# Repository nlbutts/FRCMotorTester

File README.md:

# Brushless Buddy
This is a small PCB with a display and two rotary encoders. The device
is designed to help teams quickly prototype BLC designs using the Rev SparkMax
motor controllers. Although it could be expanded to support other devices.

# Design
The block diagram is shown below. The design consists of an input buck regulator.
The regulator should be good up to 24V, but was designed to work at 12V. There
is reverse battery protection, so it should handle accidentially connecting
the battery up in reverse.

The buck generates 5V which is used for the CAN transceiver. The 5V is fed
to two LDO's to generate 3.3V for the processor and 3.0V for the LCD backlight.

There are two status LEDs on the board, two rotary encoders, and a 128x32 pixel
graphical LCD. An STM32F446 processor powers everything.

There are three user accessible connectors:
Power J2:
| Pin | Use |
| -- | -- |
| 1 | Ground |
| 2 | Power |

The mate is a **JST PHR-2**

CAN J10:
| Pin | Use |
| -- | -- |
| 1 | CAN High |
| 2 | CAN Low |
| 3 | CAN High |
| 4 | CAN Low |

The pinout is the same as the Spark MAX and uses the same connector.
The mate is a **JST PHR-4**

Aux J3:
| Pin | Use |
| -- | -- |
| 1 | 3.3V |
| 2 | Ground |
| 3 | GPIO1 |
| 4 | GPIO2 |
| 5 | GPIO3 |
| 6 | Analog Input |

The mate is a **JST PHR-6**
The auxiliary connector is used for future use cases. It just made sense to
throw this connector on.

The picture below shows the location of the connectors.

# Software
The design runs Micropython. To re-build the code do the following:
1) Download the ARM GCC compiler [GCC](https://developer.arm.com/-/media/Files/downloads/gnu/13.3.rel1/binrel/arm-gnu-toolchain-13.3.rel1-x86_64-arm-none-eabi.tar.xz)
2) Decompress the toolchain to some known location, we will call this *<gcc_emd>*
3) Open a command prompt and update your path: `export PATH=<gcc_emd>/bin:$PATH`
4) Check out this repo, we will call this directory *<repo>*
5) Navigate to *<repo>/software/micropython
6) `make -C mpy-cross -j`
7) `BOARD=FRCMOTOR make -C ports/stm32/ -j`
8) Connect the Tagconnect to the board.
9) Program **firmware.elf** using the STM32CubeProgrammer.

## SWD Debug
It is assumed you are using a JLink and it is installed in **/opt/SEGGER/JLink**
In the software directory:
1) Run **gdbstart.sh** in one terminal
2) Run debug.sh in other terminal. You now have the full power of GDB at your literial finger tips

## Python

This device runs micropython. So the main program is a Python program. The
main program is called **main.py**, catchy aint it?

There are two levels of software upgrades. If you need to upgrade the Python code,
simply update main.py and copy it over to the **PYBFLASH** device.

If you need to update Micropython, then use a terminal program to open the REPL terminal.
Hit CTRL-C to stop the program. Then type
```
import machine
machine.bootloader()
```

This will put the processor in DFU upgrade mode. You can now use STM32CubeProgrammer to program
the DFU file. If the upgrade fails, then the device will have to be JTAGed. The next rev
of the PCB will fix a defect and a physical button will allow the unit to be booted in DFU mode.

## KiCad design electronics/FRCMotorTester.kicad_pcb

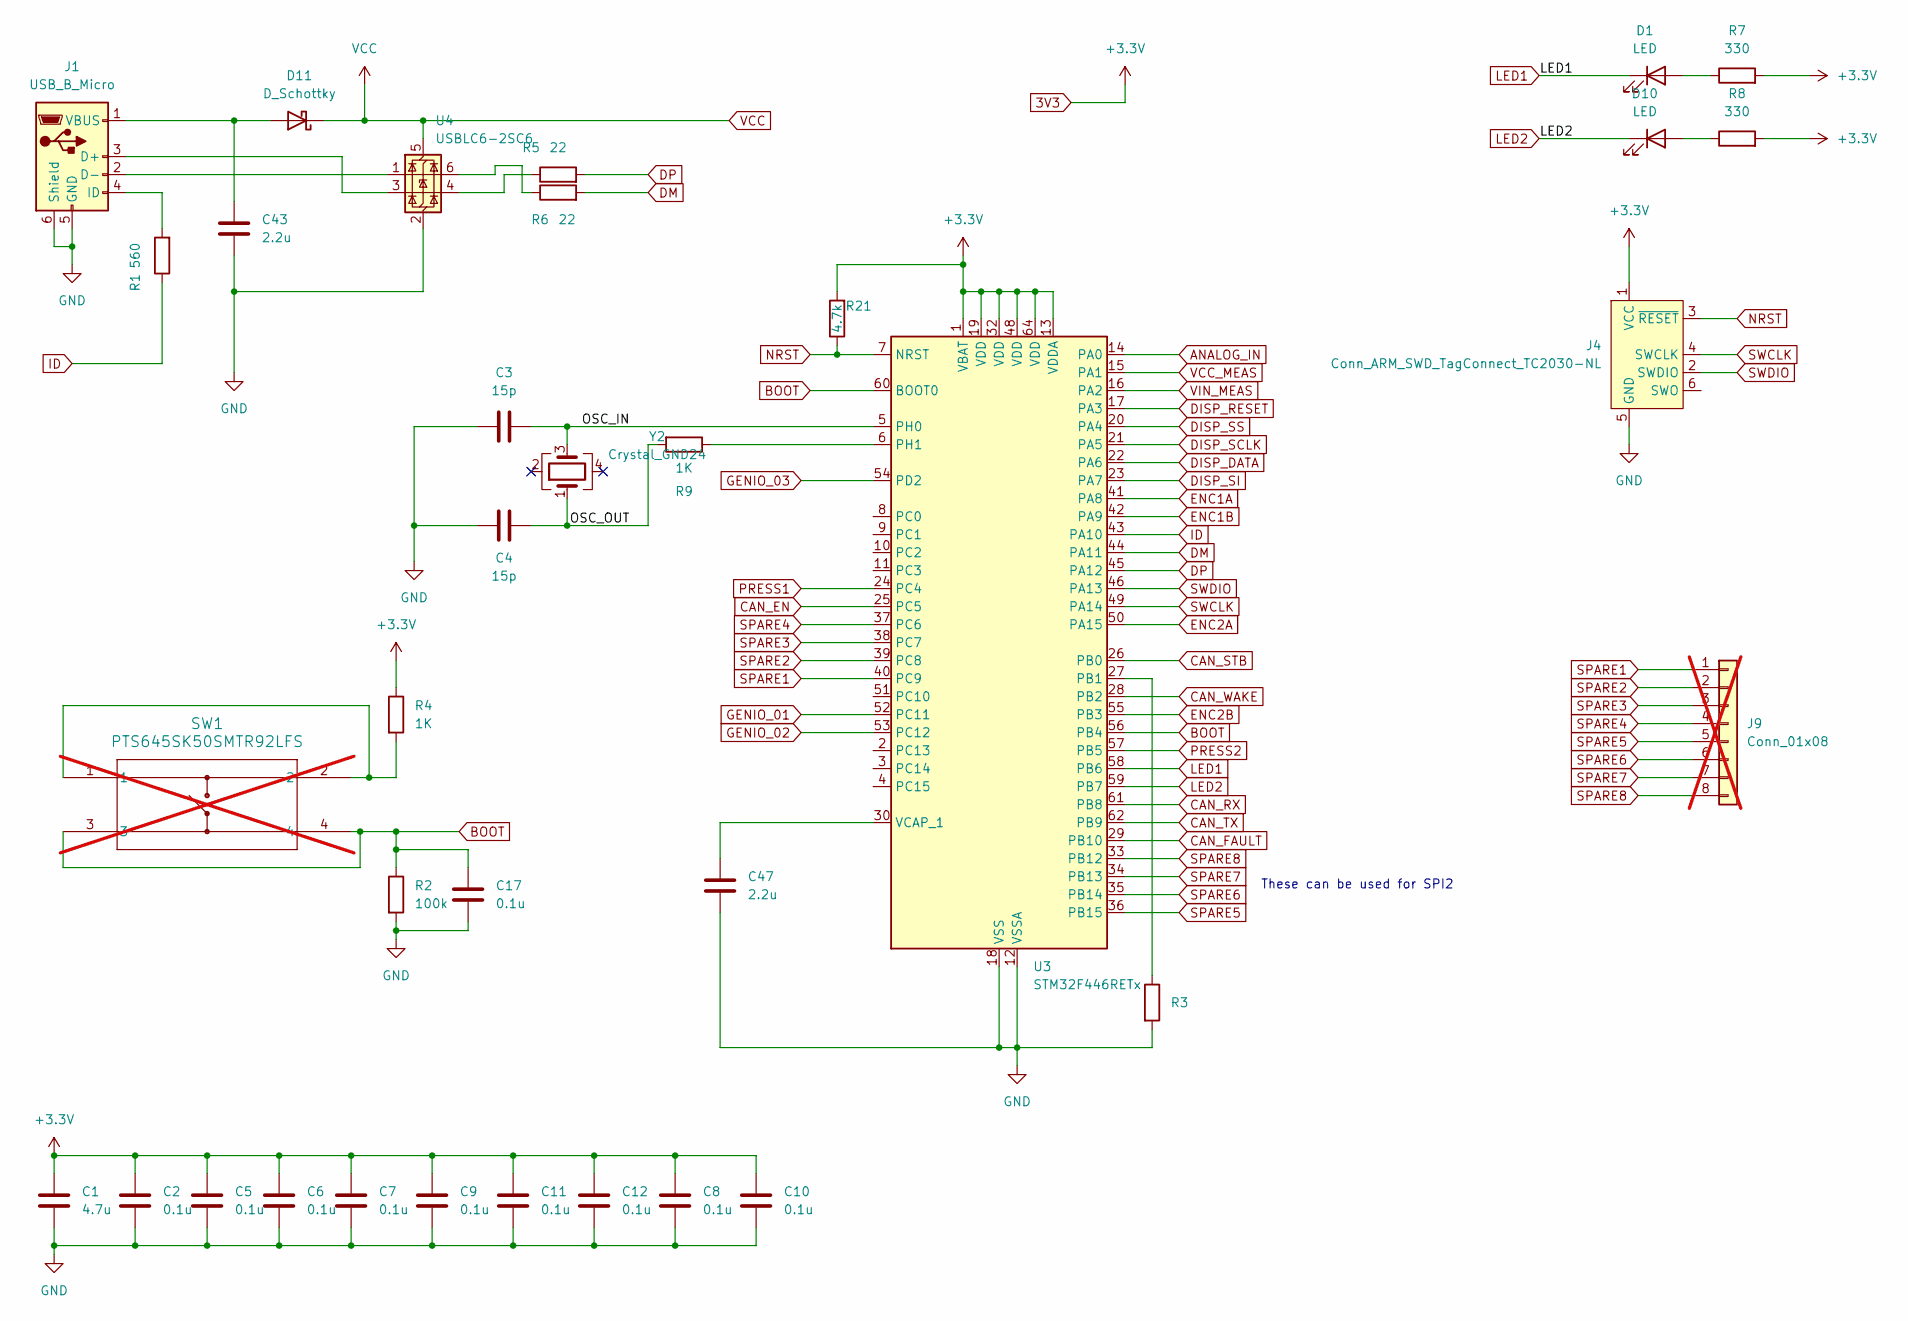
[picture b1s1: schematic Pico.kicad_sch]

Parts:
C1: 4.7u; C_0805_2012Metric; JLC C1779
C2, C5, C6, C7, C8, C9, C10, C11, C12, C17: 0.1u; C_0402_1005Metric; JLC C1525
C3, C4: 15p; C_0402_1005Metric; JLC C1548
C43, C47: 2.2u; C_0603_1608Metric; JLC C23630
D1, D10: LED; LED_0603_1608Metric; JLC C2286
D11: D_Schottky; D_SOD-123; Digikey B0540W-FDICT-ND
J1: USB_B_Micro; USB_Micro-B_Amphenol_10118193-0001LF_Horizontal; JLC C132562
J4: Conn_ARM_SWD_TagConnect_TC2030-NL; Tag-Connect_TC2030-IDC-NL_2x03_P1.27mm_Vertical
J9: Conn_01x08; PinSocket_1x08_P2.54mm_Vertical; not fitted
R1: 560; R_0603_1608Metric; JLC C23204
R2, R3: 100k; R_0603_1608Metric; JLC C25803
R4, R9: 1K; R_0402_1005Metric; JLC C11702
R5, R6: 22; R_0402_1005Metric; JLC C25092
R7, R8: 330; R_0402_1005Metric; JLC C25104
R21: 4.7k; R_0402_1005Metric; JLC C25900
SW1: PTS645SK50SMTR92LFS; PTS645SK50SMTR92LFS_CNK; JLC C221872; not fitted
U3: STM32F446RETx; LQFP-64_10x10mm_P0.5mm; JLC C69336
U4: USBLC6-2SC6; SOT-23-6; JLC C7519
Y2: Crystal_GND24; Crystal_SMD_3225-4Pin_3.2x2.5mm; JLC C156247

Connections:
3V3: C1.1, C2.1, C5.1, C6.1, C7.1, C8.1, C9.1, C10.1, C11.1, C12.1, J4.1 (VCC), R4.1, R7.2, R8.2, R21.2, U3.1 (VBAT), U3.13 (VDDA), U3.19 (VDD), U3.32 (VDD), U3.48 (VDD), U3.64 (VDD); also elsewhere on the board
/Pico/OSC_IN: C3.2, U3.5 (PH0), Y2.3
/Pico/OSC_OUT: C4.2, R9.2, Y2.1
ANALOG_IN: U3.14 (PA0); also elsewhere on the board
BOOT: C17.1, R2.1, SW1.3, SW1.4, U3.56 (PB4), U3.60 (BOOT0)
CAN_EN: U3.25 (PC5); also elsewhere on the board
CAN_FAULT: U3.29 (PB10); also elsewhere on the board
CAN_RX: U3.61 (PB8); also elsewhere on the board
CAN_STB: U3.26 (PB0); also elsewhere on the board
CAN_TX: U3.62 (PB9); also elsewhere on the board
CAN_WAKE: U3.28 (PB2); also elsewhere on the board
DISP_DATA: U3.22 (PA6); also elsewhere on the board
DISP_RESET: U3.17 (PA3); also elsewhere on the board
DISP_SCLK: U3.21 (PA5); also elsewhere on the board
DISP_SI: U3.23 (PA7); also elsewhere on the board
DISP_SS: U3.20 (PA4); also elsewhere on the board
DM: R6.2, U3.44 (PA11)
DP: R5.2, U3.45 (PA12)
ENC1A: U3.41 (PA8); also elsewhere on the board
ENC1B: U3.42 (PA9); also elsewhere on the board
ENC2A: U3.50 (PA15); also elsewhere on the board
ENC2B: U3.55 (PB3); also elsewhere on the board
GENIO_01: U3.52 (PC11); also elsewhere on the board
GENIO_02: U3.53 (PC12); also elsewhere on the board
GENIO_03: U3.54 (PD2); also elsewhere on the board
GND: C1.2, C2.2, C3.1, C4.1, C5.2, C6.2, C7.2, C8.2, C9.2, C10.2, C11.2, C12.2, C17.2, C43.1, C47.2, J1.5 (GND), J1.6 (Shield), J4.5 (GND), R2.2, R3.2, U3.12 (VSSA), U3.18 (VSS), U3.31 (VSS), U3.47 (VSS), U3.63 (VSS), U4.2 (GND); also elsewhere on the board
ID: R1.1, U3.43 (PA10)
LED1: D1.1 (K), U3.58 (PB6)
LED2: D10.1 (K), U3.59 (PB7)
NRST: J4.3 (~RESET), R21.1, U3.7 (NRST)
unnamed: D1.2 (A), R7.1
unnamed: D10.2 (A), R8.1
unnamed: C43.2, D11.2 (A), J1.1 (VBUS)
unnamed: J1.3 (D+), U4.3 (I/O2)
unnamed: J1.2 (D-), U4.1 (I/O1)
unnamed: J1.4 (ID), R1.2
unnamed: R4.2, SW1.1, SW1.2
unnamed: R5.1, U4.4 (I/O2)
unnamed: R6.1, U4.6 (I/O1)
unnamed: R3.1, U3.27 (PB1)
unnamed: R9.1, U3.6 (PH1)
unnamed: C47.1, U3.30 (VCAP_1)
PRESS1: U3.24 (PC4); also elsewhere on the board
PRESS2: U3.57 (PB5); also elsewhere on the board
SPARE1: J9.1, U3.40 (PC9)
SPARE2: J9.2, U3.39 (PC8)
SPARE3: J9.3, U3.38 (PC7)
SPARE4: J9.4, U3.37 (PC6)
SPARE5: J9.5, U3.36 (PB15)
SPARE6: J9.6, U3.35 (PB14)
SPARE7: J9.7, U3.34 (PB13)
SPARE8: J9.8, U3.33 (PB12)
SWCLK: J4.4 (SWCLK), U3.49 (PA14)
SWDIO: J4.2 (SWDIO), U3.46 (PA13)
VCC: D11.1 (K), U4.5 (VBUS); also elsewhere on the board
VCC_MEAS: U3.15 (PA1); also elsewhere on the board
VIN_MEAS: U3.16 (PA2); also elsewhere on the board

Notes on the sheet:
These can be used for SPI2

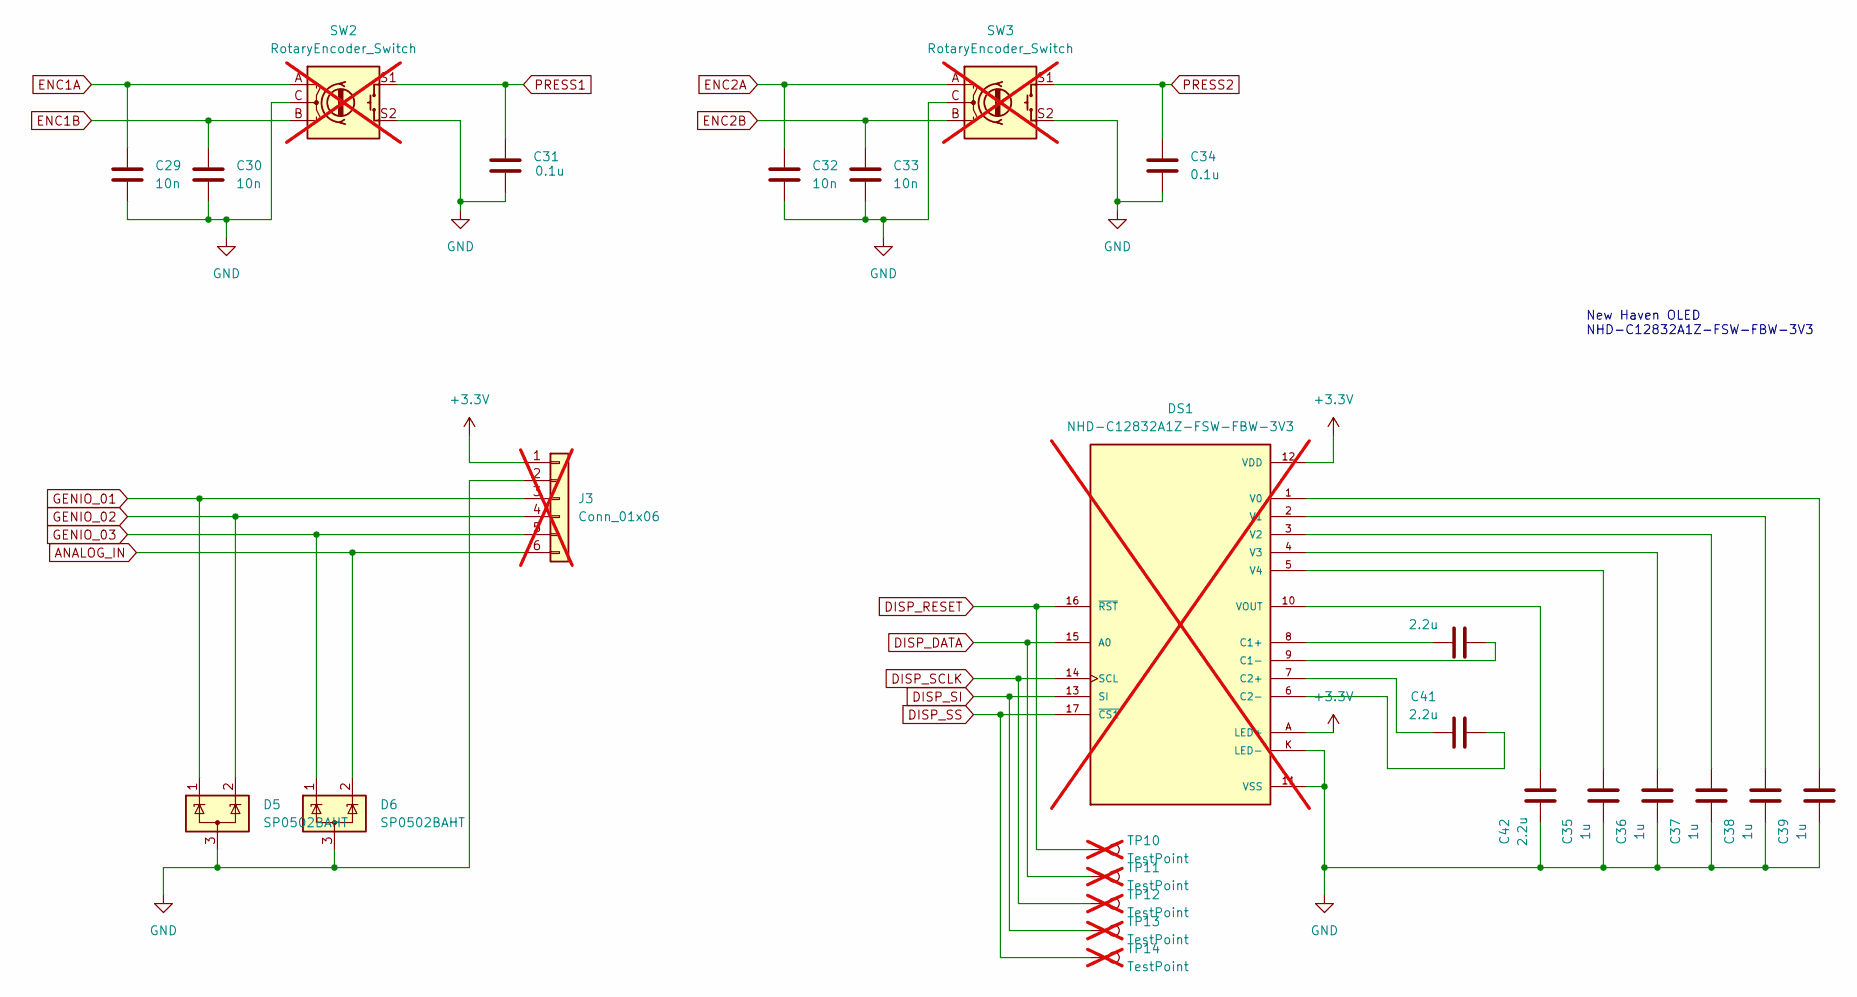
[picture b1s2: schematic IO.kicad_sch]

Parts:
C29, C30, C32, C33: 10n; C_0402_1005Metric; JLC C15195
C31, C34: 0.1u; C_0402_1005Metric; JLC C1525
C35, C36, C37, C38, C39: 1u; C_0402_1005Metric; JLC C52923
C40, C41, C42: 2.2u; C_0603_1608Metric; JLC C23630
D5, D6: SP0502BAHT; SOT-23; JLC C32677
DS1: NHD-C12832A1Z-FSW-FBW-3V3; LCD_NHD-C12832A1Z-FSW-FBW-3V3; PARTREV 7; not fitted
J3: Conn_01x06; JST_PH_S6B-PH-K_1x06_P2.00mm_Horizontal; Digikey 455-1723-ND; not fitted
SW2, SW3: RotaryEncoder_Switch; RotaryEncoder_Alps_EC11E-Switch_Vertical_H20mm; Digikey PEC11R-4220K-S0024-ND; not fitted
TP10, TP11, TP12, TP13, TP14: TestPoint; TestPoint_Pad_D1.0mm; not fitted

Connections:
3V3: DS1.12 (VDD), DS1.A (LED+), J3.1; also elsewhere on the board
ANALOG_IN: D6.2 (K), J3.6; also elsewhere on the board
DISP_DATA: DS1.15 (A0), TP11.1; also elsewhere on the board
DISP_RESET: DS1.16 (~RST), TP10.1; also elsewhere on the board
DISP_SCLK: DS1.14 (SCL), TP12.1; also elsewhere on the board
DISP_SI: DS1.13 (SI), TP13.1; also elsewhere on the board
DISP_SS: DS1.17 (~CS1), TP14.1; also elsewhere on the board
ENC1A: C29.1, SW2.A; also elsewhere on the board
ENC1B: C30.1, SW2.B; also elsewhere on the board
ENC2A: C32.1, SW3.A; also elsewhere on the board
ENC2B: C33.1, SW3.B; also elsewhere on the board
GENIO_01: D5.1 (K), J3.3; also elsewhere on the board
GENIO_02: D5.2 (K), J3.4; also elsewhere on the board
GENIO_03: D6.1 (K), J3.5; also elsewhere on the board
GND: C29.2, C30.2, C31.2, C32.2, C33.2, C34.2, C35.1, C36.1, C37.1, C38.1, C39.1, C42.1, D5.3 (A), D6.3 (A), DS1.11 (VSS), DS1.K (LED-), J3.2, SW2.C, SW2.S2, SW3.C, SW3.S2; also elsewhere on the board
unnamed: C40.1, DS1.8 (C1+)
unnamed: C40.2, DS1.9 (C1-)
unnamed: C41.1, DS1.7 (C2+)
unnamed: C41.2, DS1.6 (C2-)
unnamed: C39.2, DS1.1 (V0)
unnamed: C38.2, DS1.2 (V1)
unnamed: C37.2, DS1.3 (V2)
unnamed: C36.2, DS1.4 (V3)
unnamed: C35.2, DS1.5 (V4)
unnamed: C42.2, DS1.10 (VOUT)
PRESS1: C31.1, SW2.S1; also elsewhere on the board
PRESS2: C34.1, SW3.S1; also elsewhere on the board

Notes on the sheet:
New Haven OLED NHD-C12832A1Z-FSW-FBW-3V3

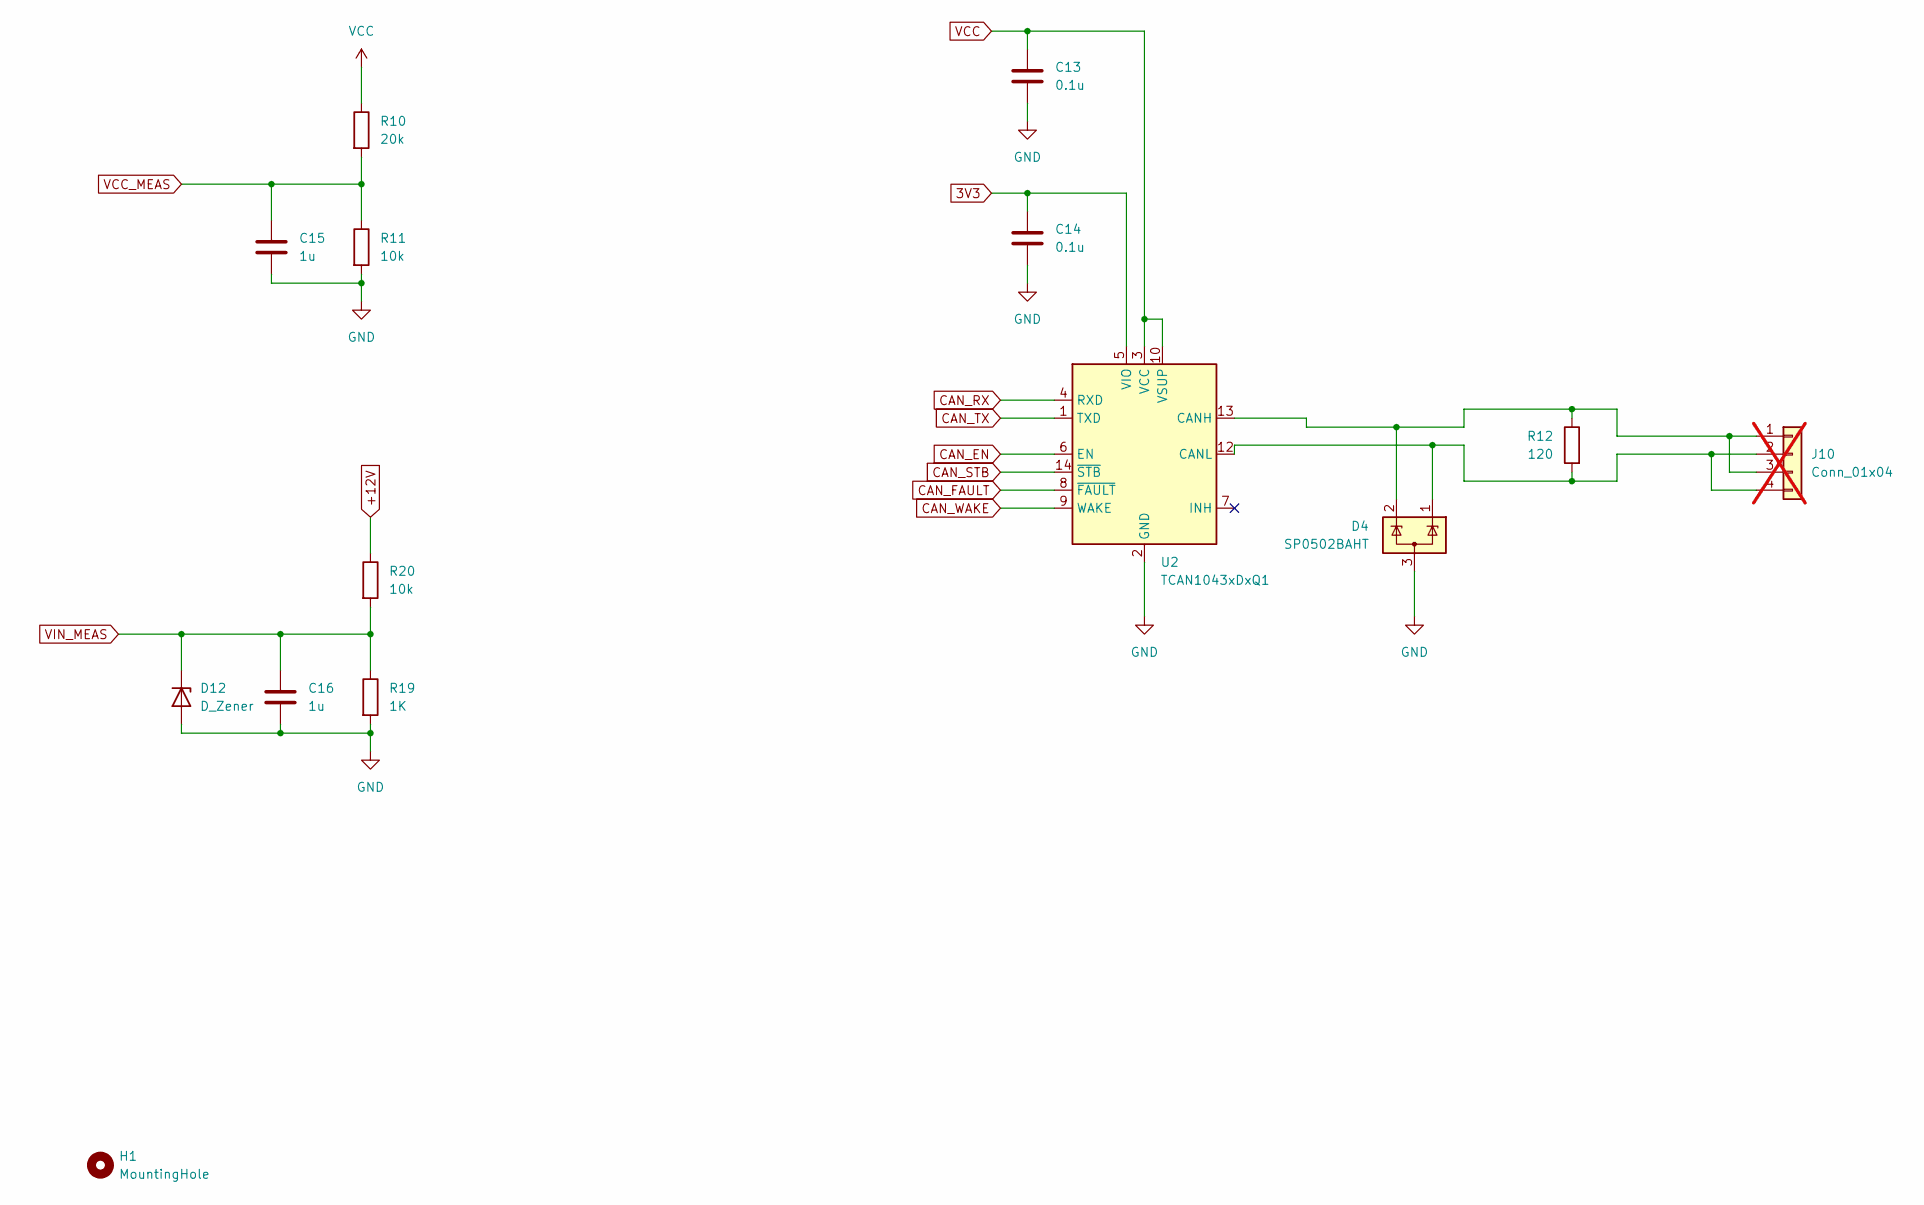
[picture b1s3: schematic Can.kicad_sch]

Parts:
C13, C14: 0.1u; C_0402_1005Metric; JLC C1525
C15, C16: 1u; C_0402_1005Metric; JLC C52923
D4: SP0502BAHT; SOT-23; JLC C32677
D12: D_Zener; D_SOD-123; JLC C2105
H1: MountingHole; brushless_buddy_logo
J10: Conn_01x04; JST_PH_S4B-PH-K_1x04_P2.00mm_Horizontal; Digikey 455-1721-ND; not fitted
R10: 20k; R_0402_1005Metric; JLC C25765
R11, R20: 10k; R_0402_1005Metric; JLC C25744
R12: 120; R_0402_1005Metric; JLC C25079
R19: 1K; R_0402_1005Metric; JLC C11702
U2: TCAN1043xDxQ1; SOIC-14_3.9x8.7mm_P1.27mm; JLC C1848115

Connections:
3V3: C14.1, U2.5 (VIO); also elsewhere on the board
+12V: R20.1; also elsewhere on the board
CAN_EN: U2.6 (EN); also elsewhere on the board
CAN_FAULT: U2.8 (~FAULT); also elsewhere on the board
CAN_RX: U2.4 (RXD); also elsewhere on the board
CAN_STB: U2.14 (~STB); also elsewhere on the board
CAN_TX: U2.1 (TXD); also elsewhere on the board
CAN_WAKE: U2.9 (WAKE); also elsewhere on the board
GND: C13.2, C14.2, C15.2, C16.2, D4.3 (A), D12.2 (A), R11.2, R19.2, U2.2 (GND); also elsewhere on the board
unnamed: D4.2 (K), J10.1, J10.3, R12.1, U2.13 (CANH)
unnamed: D4.1 (K), J10.2, J10.4, R12.2, U2.12 (CANL)
VCC: C13.1, R10.1, U2.3 (VCC), U2.10 (VSUP); also elsewhere on the board
VCC_MEAS: C15.1, R10.2, R11.1; also elsewhere on the board
VIN_MEAS: C16.1, D12.1 (K), R19.1, R20.2; also elsewhere on the board

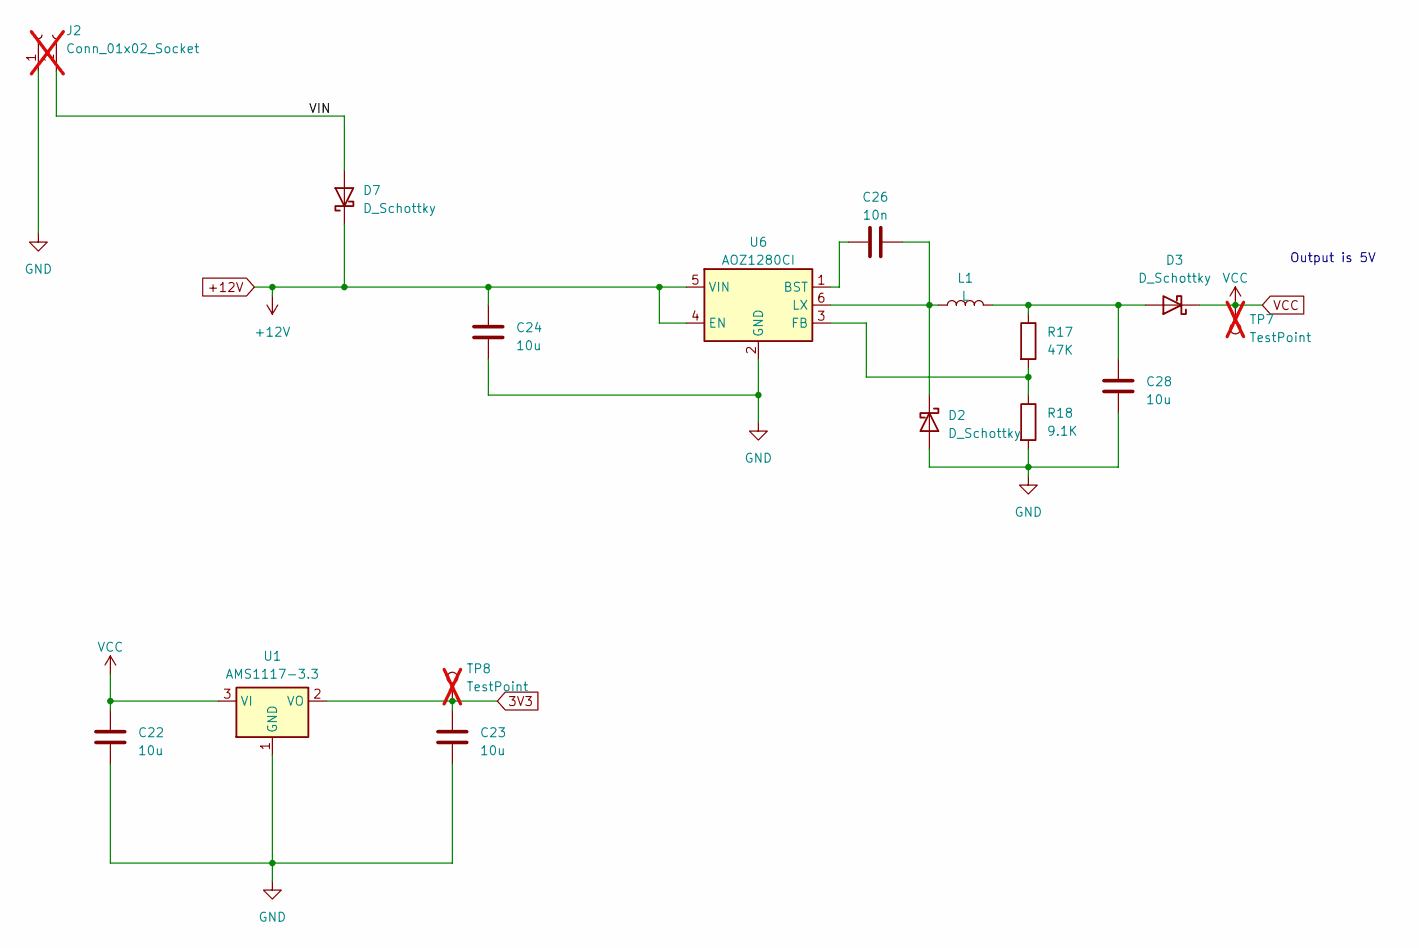
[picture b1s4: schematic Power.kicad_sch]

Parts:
C22, C23, C24, C28: 10u; C_0805_2012Metric; Digikey 490-5523-1-ND
C26: 10n; C_0402_1005Metric; Digikey 399-1092-1-ND
D2, D3, D7: D_Schottky; D_SOD-123; Digikey B0540W-FDICT-ND
J2: Conn_01x02_Socket; JST_PH_S2B-PH-K_1x02_P2.00mm_Horizontal; Digikey 455-1719-ND; not fitted
L1: L; L_1210_3225Metric; Digikey 490-15954-1-ND
R17: 47K; R_0603_1608Metric; Digikey 541-4141-1-ND
R18: 9.1K; R_0603_1608Metric; Digikey P20706CT-ND
TP7, TP8: TestPoint; TestPoint_Pad_D1.0mm; not fitted
U1: AMS1117-3.3; SOT-223-3_TabPin2; JLC C6186
U6: AOZ1280CI; SOT-23-6; Digikey 785-1277-1-ND

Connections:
3V3: C23.1, TP8.1, U1.2 (VO); also elsewhere on the board
+12V: C24.1, D7.1 (K), U6.4 (EN), U6.5 (VIN); also elsewhere on the board
/Power/VIN: D7.2 (A), J2.2
GND: C22.2, C23.2, C24.2, C28.2, D2.2 (A), J2.1, R18.2, U1.1 (GND), U6.2 (GND); also elsewhere on the board
unnamed: C26.2, D2.1 (K), L1.1, U6.6 (LX)
unnamed: C28.1, D3.2 (A), L1.2, R17.1
unnamed: C26.1, U6.1 (BST)
unnamed: R17.2, R18.1, U6.3 (FB)
VCC: C22.1, D3.1 (K), TP7.1, U1.3 (VI); also elsewhere on the board

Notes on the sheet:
Output is 5V

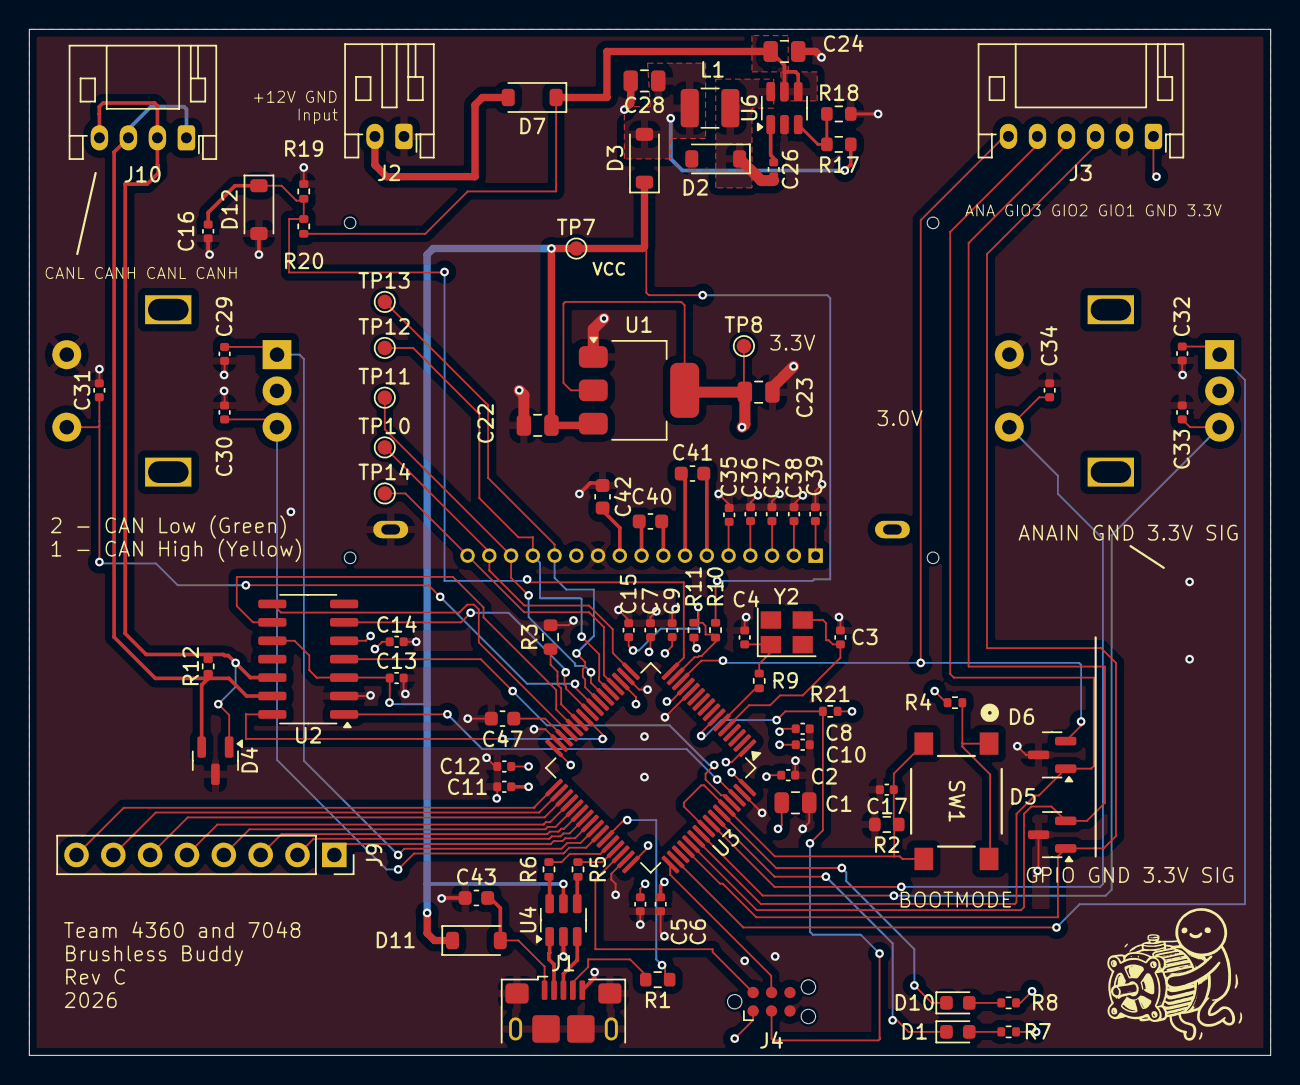
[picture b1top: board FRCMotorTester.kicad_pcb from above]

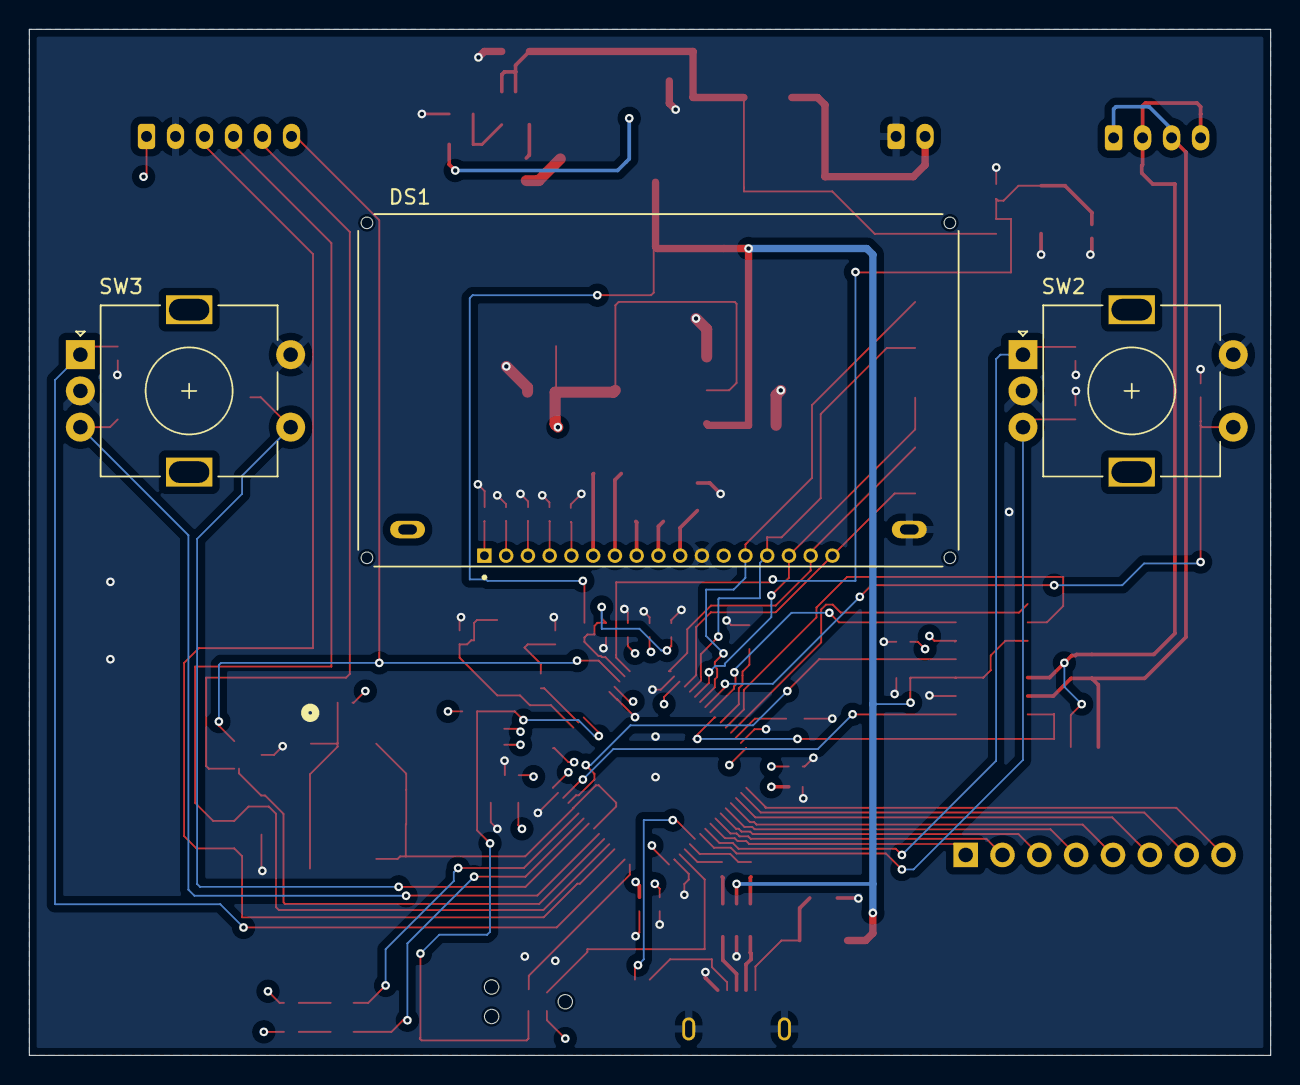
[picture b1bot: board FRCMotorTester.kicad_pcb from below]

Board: 4 copper layers, 85.6 x 70.8 mm, 90 parts (3 on the bottom side), 75 nets.

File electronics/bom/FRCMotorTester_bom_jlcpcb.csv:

Designator,Comment,Footprint,JLCPCB
C1,4.7u,Capacitor_SMD:C_0805_2012Metric,C1779
C2,0.1u,Capacitor_SMD:C_0402_1005Metric,C1525
C3,15p,Capacitor_SMD:C_0402_1005Metric,C1548
C4,15p,Capacitor_SMD:C_0402_1005Metric,C1548
C5,0.1u,Capacitor_SMD:C_0402_1005Metric,C1525
C6,0.1u,Capacitor_SMD:C_0402_1005Metric,C1525
C7,0.1u,Capacitor_SMD:C_0402_1005Metric,C1525
C8,0.1u,Capacitor_SMD:C_0402_1005Metric,C1525
C9,0.1u,Capacitor_SMD:C_0402_1005Metric,C1525
C10,0.1u,Capacitor_SMD:C_0402_1005Metric,C1525
C11,0.1u,Capacitor_SMD:C_0402_1005Metric,C1525
C12,0.1u,Capacitor_SMD:C_0402_1005Metric,C1525
C13,0.1u,Capacitor_SMD:C_0402_1005Metric,C1525
C14,0.1u,Capacitor_SMD:C_0402_1005Metric,C1525
C15,1u,Capacitor_SMD:C_0402_1005Metric,C52923
C16,1u,Capacitor_SMD:C_0402_1005Metric,C52923
C17,0.1u,Capacitor_SMD:C_0402_1005Metric,C1525
C22,10u,Capacitor_SMD:C_0805_2012Metric,C15850
C23,10u,Capacitor_SMD:C_0805_2012Metric,C15850
C24,10u,Capacitor_SMD:C_0805_2012Metric,C15850
C25,10u,Capacitor_SMD:C_0805_2012Metric,C15850
C26,10n,Capacitor_SMD:C_0402_1005Metric,C15195
C27,10u,Capacitor_SMD:C_0805_2012Metric,C15850
C28,10u,Capacitor_SMD:C_0805_2012Metric,C15850
C29,10n,Capacitor_SMD:C_0402_1005Metric,C15195
C30,10n,Capacitor_SMD:C_0402_1005Metric,C15195
C31,0.1u,Capacitor_SMD:C_0402_1005Metric,C1525
C32,10n,Capacitor_SMD:C_0402_1005Metric,C15195
C33,10n,Capacitor_SMD:C_0402_1005Metric,C15195
C34,0.1u,Capacitor_SMD:C_0402_1005Metric,C1525
C35,1u,Capacitor_SMD:C_0402_1005Metric,C52923
C36,1u,Capacitor_SMD:C_0402_1005Metric,C52923
C37,1u,Capacitor_SMD:C_0402_1005Metric,C52923
C38,1u,Capacitor_SMD:C_0402_1005Metric,C52923
C39,1u,Capacitor_SMD:C_0402_1005Metric,C52923
C40,2.2u,Capacitor_SMD:C_0603_1608Metric,C23630
C41,2.2u,Capacitor_SMD:C_0603_1608Metric,C23630
C42,2.2u,Capacitor_SMD:C_0603_1608Metric,C23630
C43,2.2u,Capacitor_SMD:C_0603_1608Metric,C23630
C47,2.2u,Capacitor_SMD:C_0603_1608Metric,C23630
D1,LED,LED_SMD:LED_0603_1608Metric,C2286
D2,D_Schottky,Diode_SMD:D_SOD-123,C8598
D3,D_Schottky,Diode_SMD:D_SOD-123,C8598
D4,SP0502BAHT,Package_TO_SOT_SMD:SOT-23,C32677
D5,SP0502BAHT,Package_TO_SOT_SMD:SOT-23,C32677
D6,SP0502BAHT,Package_TO_SOT_SMD:SOT-23,C32677
D10,LED,LED_SMD:LED_0603_1608Metric,C2286
D11,D_Schottky,Diode_SMD:D_SOD-123,C8598
D12,D_Zener,Diode_SMD:D_SOD-123,C2105
DS1,NHD-C12832A1Z-FSW-FBW-3V3,footprints:LCD_NHD-C12832A1Z-FSW-FBW-3V3,
J1,USB_B_Micro,Connector_USB:USB_Micro-B_Amphenol_10118193-0001LF_Horizontal,C132562
J2,Conn_01x02_Socket,Connector_JST:JST_PH_S2B-PH-K_1x02_P2.00mm_Horizontal,C173752
J3,Conn_01x06,Connector_JST:JST_PH_S6B-PH-K_1x06_P2.00mm_Horizontal,C471518
J10,Conn_01x04,Connector_JST:JST_PH_S4B-PH-K_1x04_P2.00mm_Horizontal,C160354
L1,L,Inductor_SMD:L_1210_3225Metric,C1330201
Q2,IRLML6401,Package_TO_SOT_SMD:SOT-23,C2593
R1,560,Resistor_SMD:R_0402_1005Metric,C25126
R2,100k,Resistor_SMD:R_0402_1005Metric,C102750
R3,100k,Resistor_SMD:R_0402_1005Metric,C102750
R4,1K,Resistor_SMD:R_0402_1005Metric,C11702
R5,22,Resistor_SMD:R_0402_1005Metric,C25152
R6,22,Resistor_SMD:R_0402_1005Metric,C25152
R7,330,Resistor_SMD:R_0402_1005Metric,C12246
R8,330,Resistor_SMD:R_0402_1005Metric,C12246
R9,1K,Resistor_SMD:R_0402_1005Metric,C11702
R10,20k,Resistor_SMD:R_0402_1005Metric,C93942
R11,10k,Resistor_SMD:R_0402_1005Metric,C25744
R12,120,Resistor_SMD:R_0402_1005Metric,C25079
R13,1.6k,Resistor_SMD:R_0402_1005Metric,C102825
R14,1k,Resistor_SMD:R_0402_1005Metric,C11702
R15,1.3k,Resistor_SMD:R_0402_1005Metric,C4906
R16,1k,Resistor_SMD:R_0402_1005Metric,C11702
R17,49.9k,Resistor_SMD:R_0402_1005Metric,C100457
R18,9.53k,Resistor_SMD:R_0402_1005Metric,C103191
R19,100k,Resistor_SMD:R_0402_1005Metric,C102750
R20,10k,Resistor_SMD:R_0402_1005Metric,C25744
R21,4.7k,Resistor_SMD:R_0402_1005Metric,C103059
SW1,PTS645SK50SMTR92LFS,footprints:PTS645SK50SMTR92LFS_CNK,C221872
U2,TCAN1043xDxQ1,Package_SO:SOIC-14_3.9x8.7mm_P1.27mm,C1848115
U3,STM32F446RETx,Package_QFP:LQFP-64_10x10mm_P0.5mm,C69336
U4,USBLC6-2SC6,Package_TO_SOT_SMD:SOT-23-6,C7519
U5,LM1117DT-ADJ,Package_TO_SOT_SMD:SOT-223-3_TabPin2,C2902259
U6,AOZ1280CI,Package_TO_SOT_SMD:SOT-23-6,C41240
U7,LM1117DT-ADJ,Package_TO_SOT_SMD:SOT-223-3_TabPin2,C2902259
Y2,Crystal_GND24,Crystal:Crystal_SMD_3225-4Pin_3.2x2.5mm,C156247

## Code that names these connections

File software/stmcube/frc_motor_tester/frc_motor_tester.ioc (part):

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Mcu.Name=STM32F405RGTx
Mcu.Package=LQFP64
Mcu.UserName=STM32F405RGTx
PA0-WKUP.Signal=ADCx_IN0
PA1.Signal=ADCx_IN1
PA10.GPIOParameters=GPIO_Label
PA10.GPIO_Label=ID
PA10.Signal=GPIO_Input
PA11.Mode=Device_Only
PA11.Signal=USB_OTG_FS_DM
PA12.Mode=Device_Only
PA12.Signal=USB_OTG_FS_DP
PA13.Mode=Serial_Wire
PA13.Signal=SYS_JTMS-SWDIO
PA14.Mode=Serial_Wire
PA14.Signal=SYS_JTCK-SWCLK
PA15.GPIOParameters=GPIO_Label
PA15.GPIO_Label=ENC2A
PA15.Signal=S_TIM2_CH1_ETR
PA2.Signal=ADCx_IN2
PA3.GPIOParameters=GPIO_Label
PA3.GPIO_Label=DISP_RESET
PA3.Signal=GPIO_Output
PA4.Mode=NSS_Signal_Hard_Output
PA4.Signal=SPI1_NSS
PA5.Mode=Simplex_Bidirectional_Master
PA5.Signal=SPI1_SCK
PA6.GPIOParameters=GPIO_Label
PA6.GPIO_Label=DISP_DATA
PA6.Signal=GPIO_Output
PA7.Mode=Simplex_Bidirectional_Master
PA7.Signal=SPI1_MOSI
PA8.GPIOParameters=GPIO_Label
PA8.GPIO_Label=ENC1A
PA8.Signal=S_TIM1_CH1
PA9.GPIOParameters=GPIO_Label
PA9.GPIO_Label=ENC1B
PA9.Signal=S_TIM1_CH2
PB0.GPIOParameters=GPIO_Label
PB0.GPIO_Label=CAN_STB
PB0.Signal=GPIO_Output
PB10.GPIOParameters=GPIO_Label
PB10.GPIO_Label=CAN_FAULT
PB10.Signal=GPIO_Input
PB12.GPIOParameters=GPIO_Label
PB12.GPIO_Label=SPARE8
PB12.Signal=GPIO_Input
PB13.GPIOParameters=GPIO_Label
PB13.GPIO_Label=SPARE7
PB13.Signal=GPIO_Input
PB14.GPIOParameters=GPIO_Label
PB14.GPIO_Label=SPARE6
PB14.Signal=GPIO_Input
PB15.GPIOParameters=GPIO_Label
PB15.GPIO_Label=SPARE5
PB15.Signal=GPIO_Input
PB2.GPIOParameters=GPIO_Label
PB2.GPIO_Label=CAN_WAKE
PB2.Signal=GPIO_Output
PB3.GPIOParameters=GPIO_Label
PB3.GPIO_Label=ENC2B
PB3.Signal=S_TIM2_CH2
PB4.GPIOParameters=GPIO_Label
PB4.GPIO_Label=SW
PB4.Signal=GPIO_Input
PB5.GPIOParameters=GPIO_Label
PB5.GPIO_Label=PRESS2
PB5.Signal=GPIO_Input
PB6.GPIOParameters=GPIO_Label
PB6.GPIO_Label=LED1
PB6.Signal=GPIO_Output
PB7.GPIOParameters=GPIO_Label
PB7.GPIO_Label=LED2
PB7.Signal=GPIO_Output
PB8.Mode=CAN_Activate
PB8.Signal=CAN1_RX
PB9.Mode=CAN_Activate
PB9.Signal=CAN1_TX
PC11.GPIOParameters=GPIO_Label
PC11.GPIO_Label=GENIO1
PC11.Signal=GPIO_Input
PC12.GPIOParameters=GPIO_Label
PC12.GPIO_Label=GENIO2
PC12.Signal=GPIO_Input
PC4.GPIOParameters=GPIO_Label
PC4.GPIO_Label=PRESS1
PC4.Signal=GPIO_Input
PC5.GPIOParameters=GPIO_Label
PC5.GPIO_Label=CAN_EN
PC5.Signal=GPIO_Output
PC6.GPIOParameters=GPIO_Label
PC6.GPIO_Label=SPARE4
PC6.Signal=GPIO_Input
PC7.GPIOParameters=GPIO_Label
PC7.GPIO_Label=SPARE3
PC7.Signal=GPIO_Input
PC8.GPIOParameters=GPIO_Label
PC8.GPIO_Label=SPARE2
PC8.Signal=GPIO_Input
PC9.GPIOParameters=GPIO_Label
PC9.GPIO_Label=SPARE1
PC9.Signal=GPIO_Input
PD2.GPIOParameters=GPIO_Label
PD2.GPIO_Label=GENIO3
PD2.Signal=GPIO_Input
PH0-OSC_IN.Mode=HSE-External-Oscillator
PH0-OSC_IN.Signal=RCC_OSC_IN
PH1-OSC_OUT.Mode=HSE-External-Oscillator
PH1-OSC_OUT.Signal=RCC_OSC_OUT
RCC.HSE_VALUE=16000000
RCC.SYSCLKFreq_VALUE=168000000
RCC.SYSCLKSource=RCC_SYSCLKSOURCE_PLLCLK
board=custom

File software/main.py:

from machine import Pin
from pyb import CAN
import pyb
import time
import sys
import struct

VERSION = 1.0

class SparkMax():
    def __init__(self, can, id, enc):
        self.can = can
        self.id = id
        self.enc = enc
        self.prev_button = 1
        self.arm = False
        self.volts = 0
        self.current = 0
        self.motor_output = 0.0
        self.enc.set_counter(0)

    def make_filter(self, class_idx):
        """Make a message filter

        Args:
            class_idx (int): combination of the API class and index
        """
        devtype = 2
        mfg = 5
        can_id = devtype << 24 | mfg << 16 | class_idx << 6 | self.id
        return can_id

    def process_button(self):
        button = self.enc.get_press()
        if not button and self.prev_button:
            self.arm = not self.arm
            if not self.arm:
                self.enc.set_counter(0)

        self.prev_button = button

    def process(self, msg):
        self.process_button()

        can_id = msg[0]
        dev = can_id & 0x3F
        api = (can_id >> 6) & 0x3FF
        if dev == self.id:
            if api == 0x61:
                data = msg[4]
                volts = ((data[6] & 0x0F) << 8) | data[5]
                self.volts = volts / 128.0
                current = data[7] << 4 | (data[6] >> 4) & 0xF
                self.current = current / 20

        if self.enc.get_counter() > 100:
            self.enc.set_counter(100)
        elif self.enc.get_counter() < -100:
            self.enc.set_counter(-100)
        self.motor_output = -(self.enc.get_counter())
        self.motor_output /= 100
        self.drive_motor(self.motor_output)

    def get_arm_str(self):
        if self.arm:
            return 'ARMD'
        return 'SAFE'

    def get_info(self):
        info = {}
        info['id'] = self.id
        info['arm'] = self.get_arm_str()
        info['volt'] = self.volts
        info['current'] = self.current
        info['output'] = self.motor_output
        return info

    def drive_motor(self, output):
        """
        Driving motor 2 uses this message: DevID: 0 idx: 2 cls: 11 mfg: 5 devtype: 2 raw: 02052C80 data: 04 00 00 00 00 00 00 00
        At -0.12 DevID: 2 idx: 2 cls: 0 mfg: 5 devtype: 2 raw: 02050082 data: 8F C2 F5 BD 00 00 00 00
        Driving motor 4 uses this message: DevID: 0 idx: 2 cls: 11 mfg: 5 devtype: 2 raw: 02052C80 data: 10 00 00 00 00 00 00 00
        """
        if self.arm:
            devtype = 2
            mfg = 5
            cls = 0
            idx = 2
            can_id = devtype << 24 | mfg << 16 | cls << 10 | idx << 6 | self.id
            data = struct.pack('<fBBBB', output, 0, 0, 0, 0)  # Format the payload
            self.can.send(data, can_id, extframe=True)  # Send the CAN message

    def debug_can(self, message):
        """Debug the can message

        Args:
            message (_type_): _description_
        """
        id = message[0]
        devtype = id >> 24
        mfg = (id >> 16) & 0xFF
        cls = (id >> 10) & 0x3F
        idx = (id >> 6) & 0xF
        devid = id & 0x3F
        s = f'DevID: {devid} idx: {idx} cls: {cls} mfg: {mfg} devtype: {devtype} raw: {id:08X} data: '
        for b in message[4]:
            s += f'{b:02X} '
        print(s)

def get_spark_max_ids(can, delay=2):
    try:
        ids = {}
        start = time.time()
        while time.time() - start < delay:
            m = can.recv(0)
            id = m[0] & 0x3F
            if id > 0:
                ids[id] = 1
        print(ids)
        return list(ids.keys())
    except:
        return []

class Encoder():
    def __init__(self, enc_name):
        if 'Left' in enc_name:
            self.pin_a = Pin('ENC2A', Pin.AF_PP, pull=Pin.PULL_UP, af=Pin.AF1_TIM2)
            self.pin_b = Pin('ENC2B', Pin.AF_PP, pull=Pin.PULL_UP, af=Pin.AF1_TIM2)
            self.press = Pin('PRESS2', Pin.IN, pull=Pin.PULL_UP)
            self.tim = pyb.Timer(2, prescaler=0, period=100)
            self.ch = self.tim.channel(1, pyb.Timer.ENC_AB)
        elif 'Right' in enc_name:
            self.pin_a = Pin('ENC1A', Pin.AF_PP, pull=Pin.PULL_UP, af=Pin.AF1_TIM1)
            self.pin_b = Pin('ENC1B', Pin.AF_PP, pull=Pin.PULL_UP, af=Pin.AF1_TIM1)
            self.press = Pin('PRESS1', Pin.IN, pull=Pin.PULL_UP)
            self.tim = pyb.Timer(1, prescaler=0, period=100)
            self.ch = self.tim.channel(1, pyb.Timer.ENC_AB)

    def get_press(self):
        return self.press.value()

    def get_counter(self):
        return self.tim.counter() - 500

    def set_counter(self, value):
        self.tim.counter(500 + value)

sw = Pin('SW', Pin.IN)
prev = sw.value()

lcd = pyb.LCD('X')

can_txd = Pin('CAN_TX', Pin.AF_PP, af=Pin.AF9_CAN1)
can_rxd = Pin('CAN_RX', Pin.AF_PP, af=Pin.AF9_CAN1)

can_en = Pin('CAN_EN', Pin.OUT)
can_fault = Pin('CAN_FAULT', Pin.IN)
can_wake = Pin('CAN_WAKE', Pin.OUT)
can_stb = Pin('CAN_STB', Pin.OUT)

can_en.value(1)
can_fault.value(1)
can_wake.value(1)
can_stb.value(1)

# Initialize CAN bus
can = CAN(1, CAN.NORMAL)

# Configure the CAN bus settings
can.init(CAN.NORMAL, prescaler=2, sjw=1, bs1=14, bs2=6, auto_restart=True)
can.setfilter(0, can.MASK32, 0, (0, 0), extframe=True)
can.send('hello', 0, extframe=True)

leftEnc = Encoder('Left')
rightEnc = Encoder('Right')

def show_boot_screen(can_ids=[]):
    lcd.fill(0)
    lcd.text(f'Brushless Buddy', 0, 0, 1)
    lcd.text(f'Ver: {VERSION}', 0, 10, 1)
    if len(can_ids) > 0:
        s = 'Found: '
        for id in can_ids:
            s += f'{id} '
        lcd.text(s, 0, 20, 1)
    else:
        lcd.text(f'Found: None', 0, 20, 1)
    lcd.show()

show_boot_screen()
ids = sorted(get_spark_max_ids(can))
print(f'Found ids: {ids}')

if len(ids) > 2:
    lcd.fill(0)
    lcd.text('Too many CAN', 0, 0, 1)
    lcd.text('nodes on bus', 0, 10, 1)
    lcd.show()
    time.sleep(5)
    sys.reset()
if len(ids) == 0:
    lcd.fill(0)
    lcd.text('No SparkMaxs', 0, 0, 1)
    lcd.text('detected', 0, 10, 1)
    lcd.text('rebooting', 0, 20, 1)
    lcd.show()
    time.sleep(5)
    machine.reset()

motors = []
if len(ids) == 1:
    motors.append(SparkMax(can, ids[0], leftEnc))
elif len(ids) == 2:
    motors.append(SparkMax(can, ids[0], leftEnc))
    motors.append(SparkMax(can, ids[1], rightEnc))

#debug_can(can, 0)

start = time.time()
while True:
    msg = can.recv(0)
    motor_info = []
    arm_field = 0
    for motor in motors:
        motor.process(msg)
        motor_info.append(motor.get_info())
        if motor.arm:
            arm_field |= 1 << motor.id

    # Send the heartbeat message
    can_id = 0x02052C80
    data = struct.pack('<II', arm_field, 0)
    can.send(data, can_id, extframe=True, timeout=100)

    if time.time() - start > 0.1:
        start = time.time()
        lcd.fill(0)
        if len(motor_info) == 1:
            lcd.text(f'{motor_info[0]['id']}/{motor_info[0]['arm']}', 0, 0, 1)
            lcd.text(f'{motor_info[0]['output']}', 0, 10, 1)
            lcd.text(f'{motor_info[0]['volt']:.1f}/{motor_info[0]['current']}', 0, 20, 1)
        else:
            str = f'{motor_info[0]['id']}/{motor_info[0]['arm']} | {motor_info[1]['arm']}/{motor_info[1]['id']}'
            lcd.text(str, 0, 0, 1)

            str = f'{motor_info[0]['output']:5.2f}  | {motor_info[1]['output']:5.2f}'
            lcd.text(str, 0, 10, 1)

            str = f'{motor_info[0]['volt']:.1f}V/ {motor_info[0]['current']:2.1f} / {motor_info[1]['current']:2.1f}'
            lcd.text(str, 0, 20, 1)
        lcd.show()
